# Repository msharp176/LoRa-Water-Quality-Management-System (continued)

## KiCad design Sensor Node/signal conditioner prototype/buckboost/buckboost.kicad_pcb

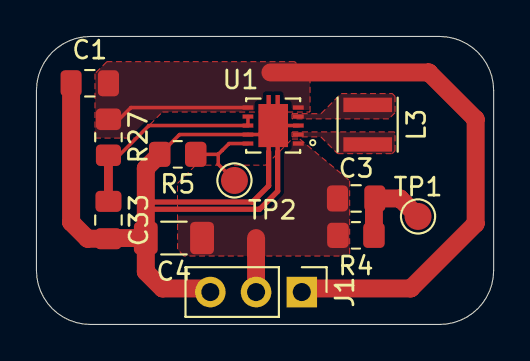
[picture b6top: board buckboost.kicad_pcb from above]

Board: 2 copper layers, 25.4 x 16.0 mm, 12 parts (0 on the bottom side), 8 nets.

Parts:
C1: 22uF; C_0805_2012Metric_Pad1.18x1.45mm_HandSolder
C3: 4p; C_0805_2012Metric_Pad1.18x1.45mm_HandSolder
C4: 47uF; C_1206_3216Metric_Pad1.33x1.80mm_HandSolder
C33: 100n; C_0805_2012Metric_Pad1.18x1.45mm_HandSolder
J1: Conn_01x03_Pin; PinHeader_1x03_P2.54mm_Vertical
L3: 2.2uH; IND_LQH3NPZ2R2MMEL
R4: 560k; R_0805_2012Metric_Pad1.20x1.40mm_HandSolder
R5: 100k; R_0805_2012Metric_Pad1.20x1.40mm_HandSolder
R27: 100R; R_0805_2012Metric_Pad1.20x1.40mm_HandSolder
TP1, TP2: TestPoint; TestPoint_Pad_D1.5mm
U1: TPS63000; CONV_TPS63000DRCR

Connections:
+3V3: C3.1, C4.1, J1.2, R4.1, U1.1 (VOUT)
/Buck-Boost Regulator Layout/FB: R5.1, TP2.1, U1.10 (FB)
/V_{IN}: C1.1, J1.1, R27.1, U1.5 (VIN), U1.6 (EN)
GND: C1.2, C4.2, C33.2, J1.3, R5.2, U1.3 (PGND), U1.9 (GND), U1.11 (PGND), U1.11_1 (PGND), U1.11_2 (PGND), U1.11_3 (PGND), U1.11_4 (PGND)
unnamed: C3.2, R4.2, TP1.1
unnamed: L3.2, U1.4 (L1)
unnamed: L3.1, U1.2 (L2)
unnamed: C33.1, R27.2, U1.7 (PS/SYNC), U1.8 (VINA)

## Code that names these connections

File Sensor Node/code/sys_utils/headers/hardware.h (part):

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#define SPI0_SCK GP18

#define EN_5V GP2
#define STATUS_LED GP3
#define TX_LED GP4
#define RX_LED GP5
#define ERR_LED GP6

#pragma region GPIO Aliases

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
typedef struct tmux1309_context_s {
    const uint8_t enable;               // Enable Pin (active low)
    const uint8_t sel0;                 // Select 0 Pin
    const uint8_t sel1;                 // Select 1 Pin
} tmux1309_context_t;

/**
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
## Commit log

2025-04-18 test commit
2025-04-21 Developed initial simulation for the turbidity sensor. Simulation files (.asc) are to be ran in LTSpice. Wrote a brief program that models the turbidity sensor in a PWL (piecewise linear) file which 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
2025-04-21 woops. would have destroyed the ADC on the pico with that. Added a zener diode at the output to cap the output voltage to 3V.
2025-04-21 Updated resistor values to get response more spread out within the desired NTU range.
2025-04-25 Add final proposal PDF
2025-05-03 Add preliminary sensor node BOM and corresponding datasheets
2025-06-21 Folder restructuring. Add Development log for Sensor Node.
2025-06-26 Add prototype sx126x driver source and HAL, custom project-level HAL, and basic SPI testing logic.
2025-07-04 Add prototype LoRa module driver code, folder restructuring, expanded HAL, interrupt servicing, and example HAL functionality for future reference.
2025-08-01 Finalized a working driver for the sx1262 LoRa module using the Raspberry Pi Pico 2. Add a prototype sx1262 schematic and testbench drawing.
2025-08-04 Add preliminary layout designs for the RP2350 and Buck-Boost Regulator DC Power Supply. Added datasheets and updated the development log.
2025-08-07 Add finalized schematics for sx1262 and SPI flash.
2025-08-11 Finalize first draft schematic capture, assign all footprints, and begin preliminary PCB layout.
2025-08-11 Add a DC offset to the PH sensor input to make it single-ended supply compatible.
2025-08-12 Turbidity Sensor Notes/Schematics/Datasheets
2025-08-12 Add power supply PCB layout
2025-08-12 Begin RP2350 PCB layout
2025-08-13 finalize RP2350 layout (mostly)
2025-08-13 Finalize most routing, preliminary RF design (fencing/stitching vias) RF transmission line trace, etc.
2025-08-14 Improved RF routing, import all 3D models.
2025-08-14 Improve RF routing and noise immunity. Add copper pours on top and bottom layer with ample stitching vias. Add TVS diodes for ESD protection and testpoints for hardware debugging.
2025-08-15 Resolve JLCPCB DFM issues
2025-08-15 Add indicator LEDs, PCB cleanup, and preliminary BOM, assuming R/C can be sourced from equipment room.
2025-08-18 Change connectors to reduce component cost, identified R/C components for purchase.
2025-08-18 PCB design cleanup, update footprints,3D models. Denote board as variant 'A', using the quad op-amp design.
2025-08-19 Add PCB "B" variant, which uses INA333 and LMV321 instead of discrete instrumentation amplifier.
2025-08-19 Add BOM
2025-08-19 Add correct BOM (sorry)
2025-08-20 Add preliminary changes based on feedback from Zach Martin.
2025-08-20 oops
2025-08-21 Update all R/C components to 0805, complete layout of updated buck-boost converter. Add TVS diodes for ESD protection on vulnerable signals, add reference designators, and fix clearance issues.
2025-08-21 Board Cleanup
    Cleanup traces, fix minor layout issues. Create updated BOM
2025-08-22 added ph sensor code
2025-08-28 Minor modifications to PCB design, add prototyping design for signal conditioner. Finalize documentation for the first draft PCB.
2025-09-03 Finalize changed to prototype signal conditioner PCB for manufacture.
2025-09-10 Add files via upload
    Data set that will be used to train NN
2025-09-13 Add test pcb designs and simulations for signal conditioner, drivers for digital potentiometer, analog mux, and spi flash.
2025-09-17 Finalize PCB for order
2025-09-22 Working LoRa driver! Transmit and receive operations are now both validated working.
2025-09-24 Working AES128 encryption, add CJSON Source
2025-10-08 Add driver for ADC and other breakout board designs.
2025-10-31 Implemented RDT3.0 for LoRa data transfer.
2025-11-08 Add dedicated receiver code, begin developing code for software-defined instrumentation amplifier.
2025-11-11 Add receiver gerber files and updated testing CSVs.
2025-11-18 Finalize working software-defined instrumentation amplifier driver code and signal acquisition, begin prototyping sensor data conversion methods. Add hardware changes needed for expected operation of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
2025-12-03 Add finalized firmware - implemented power savings mode and implemented complete FSM.
2025-12-09 Add watchdog timer to main firmware FSM
2025-12-10 Added Dashboard Code
2025-12-12 Add final changes to schematics for documentation purposes
2025-12-12 Complete repository restructuring and organization for submission with final report.
2025-12-13 Add files via upload
    MATLAB files for data cleaning, data formatting, and NN training
2025-12-15 Organize neural net code, minor updates to files
